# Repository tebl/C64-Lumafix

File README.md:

# C64 Lumafix

Based on Lumafix64 by e5frog over at the lemon64.com forums, this is a somewhat simplified version that should be easier to solder together for beginners with access to a reasonable set of soldering tools. Gone are the slightly confusing surface mount options that's mostly only suitable for those with more advanced skills or aim to have them premade with components from a fabrication company.

For those not familiar with the Lumafix board, this is a board that attempts to minimize the amount of vertical banding that to some extent occurrs on most Commodore 64 computers when connected to a modern TV (C64C and other short boards seem to be affected the most). It doesn't remove the problem completely since it doesn't solve the root cause of them, but it cancels out most of the effect - granting you the best visual clarity you can get from the original hardware! The board plugs in between the VIC-II chip and your Commodore 64 motherboard.

All of the components have, where applicable, been picked out so that it can be built as cheap as possible for people wanting to do this as a fun project in the home workshop (or kitchen table if that is what you have). For a complete list of components, see the BOM below. 

## Building the board
The recommended sequence of components to be soldered in place is as follows:

1. Check errata below for relevant changes
2. Read through the secion "Signal bypass" below if you have a revision B or later board, decide which functionality you want the board to have.
2. Solder in place the round pin headers into the position marked U2, the 40 pin strip should be cut in half so that you have two sections with 20 pins each. Take a look at the PCB, see two sections with 2x20 holes in them? These pins should be soldered on the top side of the PCB in the right set of 20 pin holes. The rest of the components from here on in are soldered on the backside as usual! You can use a spare 40 pin socket to ensure that the pins line up nicely before soldering them in place, if the board is going into a Commodore 64C you should shorten the pins with so that the board fits flush with the socket.
2. Solder in the three ceramic capacitors, note that C3 has a different value than the other two.
3. Solder in a 40 pin socket for U3, a 14 pin socket for U1. Note that sockets have an indent on one side indicating pin 1, this should be matched to a similar indent on the PCB silkscreen.
4. Solder the three potentiometers into place with the adjustment screw down towards the bottom. Temporarily hold them in place using tape to get the orientation just right if you like everything to be lined up perfectly, solder one pin in place and change orientation - heat up solder joint and reorient it until satisfied. Solder the rest of the pins now!

Inspect the board thoroughly until you are satisfied that none of the pins haven't been shorted together, to get a clean finish I recommend cleaning away any flux residue with some nail-polish remover without perfume (dilute it with a little IPA). Finally clean it again using IPA and some cotton buds. If you have access to the stuff, there are dedicated PCB-cleaning solutions that can be purchased though the first option can be easier to get depending on where you live.

### Signal bypass
When developing the [C64 Modulator Replacement](https://github.com/tebl/C64-Modulator-Replacement), there was an increase in the amount of visible jailbars on the screen (of the kind the Lumafix was made to smoothe over). This is due to crosstalk between video signals travelling across the motherboard in close proximity to other signals, the Lumafix attempts to remove these by adding the reverse of the same signals. I did however find that most of the issues disappear if the signals are run directly between the modulator board and the Lumafix with most of the circuitry no longer needed in this combination - video signals are wired directly to the modulator instad (bypassing the noise on the motherboard itself).

- If you want to build a standard revision B Lumafix board **without** replacing the modulator, then you should install two pieces of wire across the two jumpers marked CHR_SEP and LUM_SEP.
- If you want to build a standard revision B Lumafix board for use **with** the modulator replacement, install a piece of wire across pin 1-2 of the bottom potentiometer footprint. Run CHR/LUM wires from Lumafix board to the modulator replacement.

### Errata
- No issues noted so far, but thanks for checking!

## Installing the board
Did all the checking for shorts, board cleaning and ready to continue? If not, do so now (I'll wait)! Locate the VIC-II chip, it's a 40 pin IC like the board we just soldered together - mine was marked 8565 - to be sure you get the right one, check the [Wikipedia](https://en.wikipedia.org/wiki/MOS_Technology_VIC-II#List_of_VIC-II_versions) site for various IC version numbers to look for.

Now, this Commodore 64 you've opened up is probably over 30 years old so don't touch anything that you don't need to. When removing the IC it may appear stuck - don't yank on it, just carefully ease it out. If you don't have a dedicated IC-extractor, you _can_ use a flat screwdriver - just loosen it slightly from each side until it comes loose, take care not to scrape it against the motherboard under the socket! Insert the extracted IC into the board you just built, matching the indent to the socket while taking care that all pins goes into the socket and don't get stuck or bent underneath it. Insert the board into the now empty socket on the motherboard, taking care to match the orientation to the socket.

Turn all the potentiometers anti-clockwise all the way until you can hear you're at the beginning, with the Commodore 64 adjust the top one until you get the picture as good as it can get. The middle one will dial it in the rest of the way until you are completely satisfied with the startup screen on the Commodore 64. The bottom potentiometer adjusts phase-variance on the color signal, for this you may need to play around with it until you are satisfied with the results - mostly this will help alleviate slight ghosting effects on coloured objects on the screen, but for the most part just dial in the prettiest blue startup screen you can find and come back to it later if you find that you need to.

Note that the values dialed in will be very specific for the TV you'll be using, so test it out on the TV-setup you'll be using. Some TVs need more help than others, if you're lucky enough to still own a CRT you probably won't need this in the first place!

If you decided to build a revision B, or later version, of the Lumafix with signal bypass you need to run wires directly from the top of the board to the relevant points on the modulator replacement (these are labelled LUM and CHR on both boards, wire to the top pads on the modulator replacement board).

# Schematic
The supplied KiCad files should be sufficient as both a schematic and as a  starting point for ordering PCBs (basically you could just zip the contents of the export folder and upload that on a fabrication site), the schematic is also available in [PDF-format](https://github.com/tebl/C64-Lumafix/raw/master/export/Lumafix.pdf) and this is what you'll need to print and work your way through this things don't work as expected after assembly.

# BOM
Most parts should be easy to get a hold of from your favourite local electronic component shop, but given that I don't have access to such shops where I live so everything was based on whatever I could get cheapest from ebay/AliExpress (free shipping, plan on usually waiting 3-4 weeks though). You don't need the newest and fastest components, after all it's going into a 80s-era computer so don't go overboard unless you want to (you can replace 74LS ICs with 74HCT or 74ALS if you want something newer). Most components have been produced by various manufacturers, these mostly do the same thing without any relevant differences so just go for the cheapest.

Some vendors will have the same ICs in different form factors, the ones you want will often be specified as being in the form of a DIP/PDIP package. Usually you'll want sockets for each of the ICs as well, a bag of assorted sockets should be easily available without setting you back more than a couple bucks. With the sockets in place, you don't need to dread having to remove an IC later, this leads to easier fault finding and you can even "borrow" them for other projects later! For the pin headers, you should order the round pin ones since the standard ones will easily break the IC socket and you don't want to save pennies if it costs you a Commodore 64 mainboard!

| Reference    | Item                                  | Count |
| ------------ | ------------------------------------- | ----- |
| PCB          | Fabricate using Gerber files ([order](https://www.pcbway.com/project/shareproject/Commodore_64_Lumafix__revision_B_.html?inviteid=88707))  |     1 |
| C1-C2        | 47pf ceramic capacitor                |     2 |
| C3           | 100nF ceramic capacitor               |     1 |
| U1           | 74LS14 DIP-14                         |     1 |
| U2           | 40 pin round pin header (break in 2)  |     1 |
| U3           | DIP-40 IC Socket                      |     1 |
| RV1-RV3      | 3296W Potentiometer 2k Ohm            |     3 |

Please use the order link above when signing up to help me support this project, I'll get a small discount on future orders and hopefully that means I can afford to keep developing new and exciting modules in the future. By using the URL you won't have to deal with the rather daunting order forms for PCB fabrication, but if you want to go that route they'll probably want a zipped-up copy of the files in the export-directory!

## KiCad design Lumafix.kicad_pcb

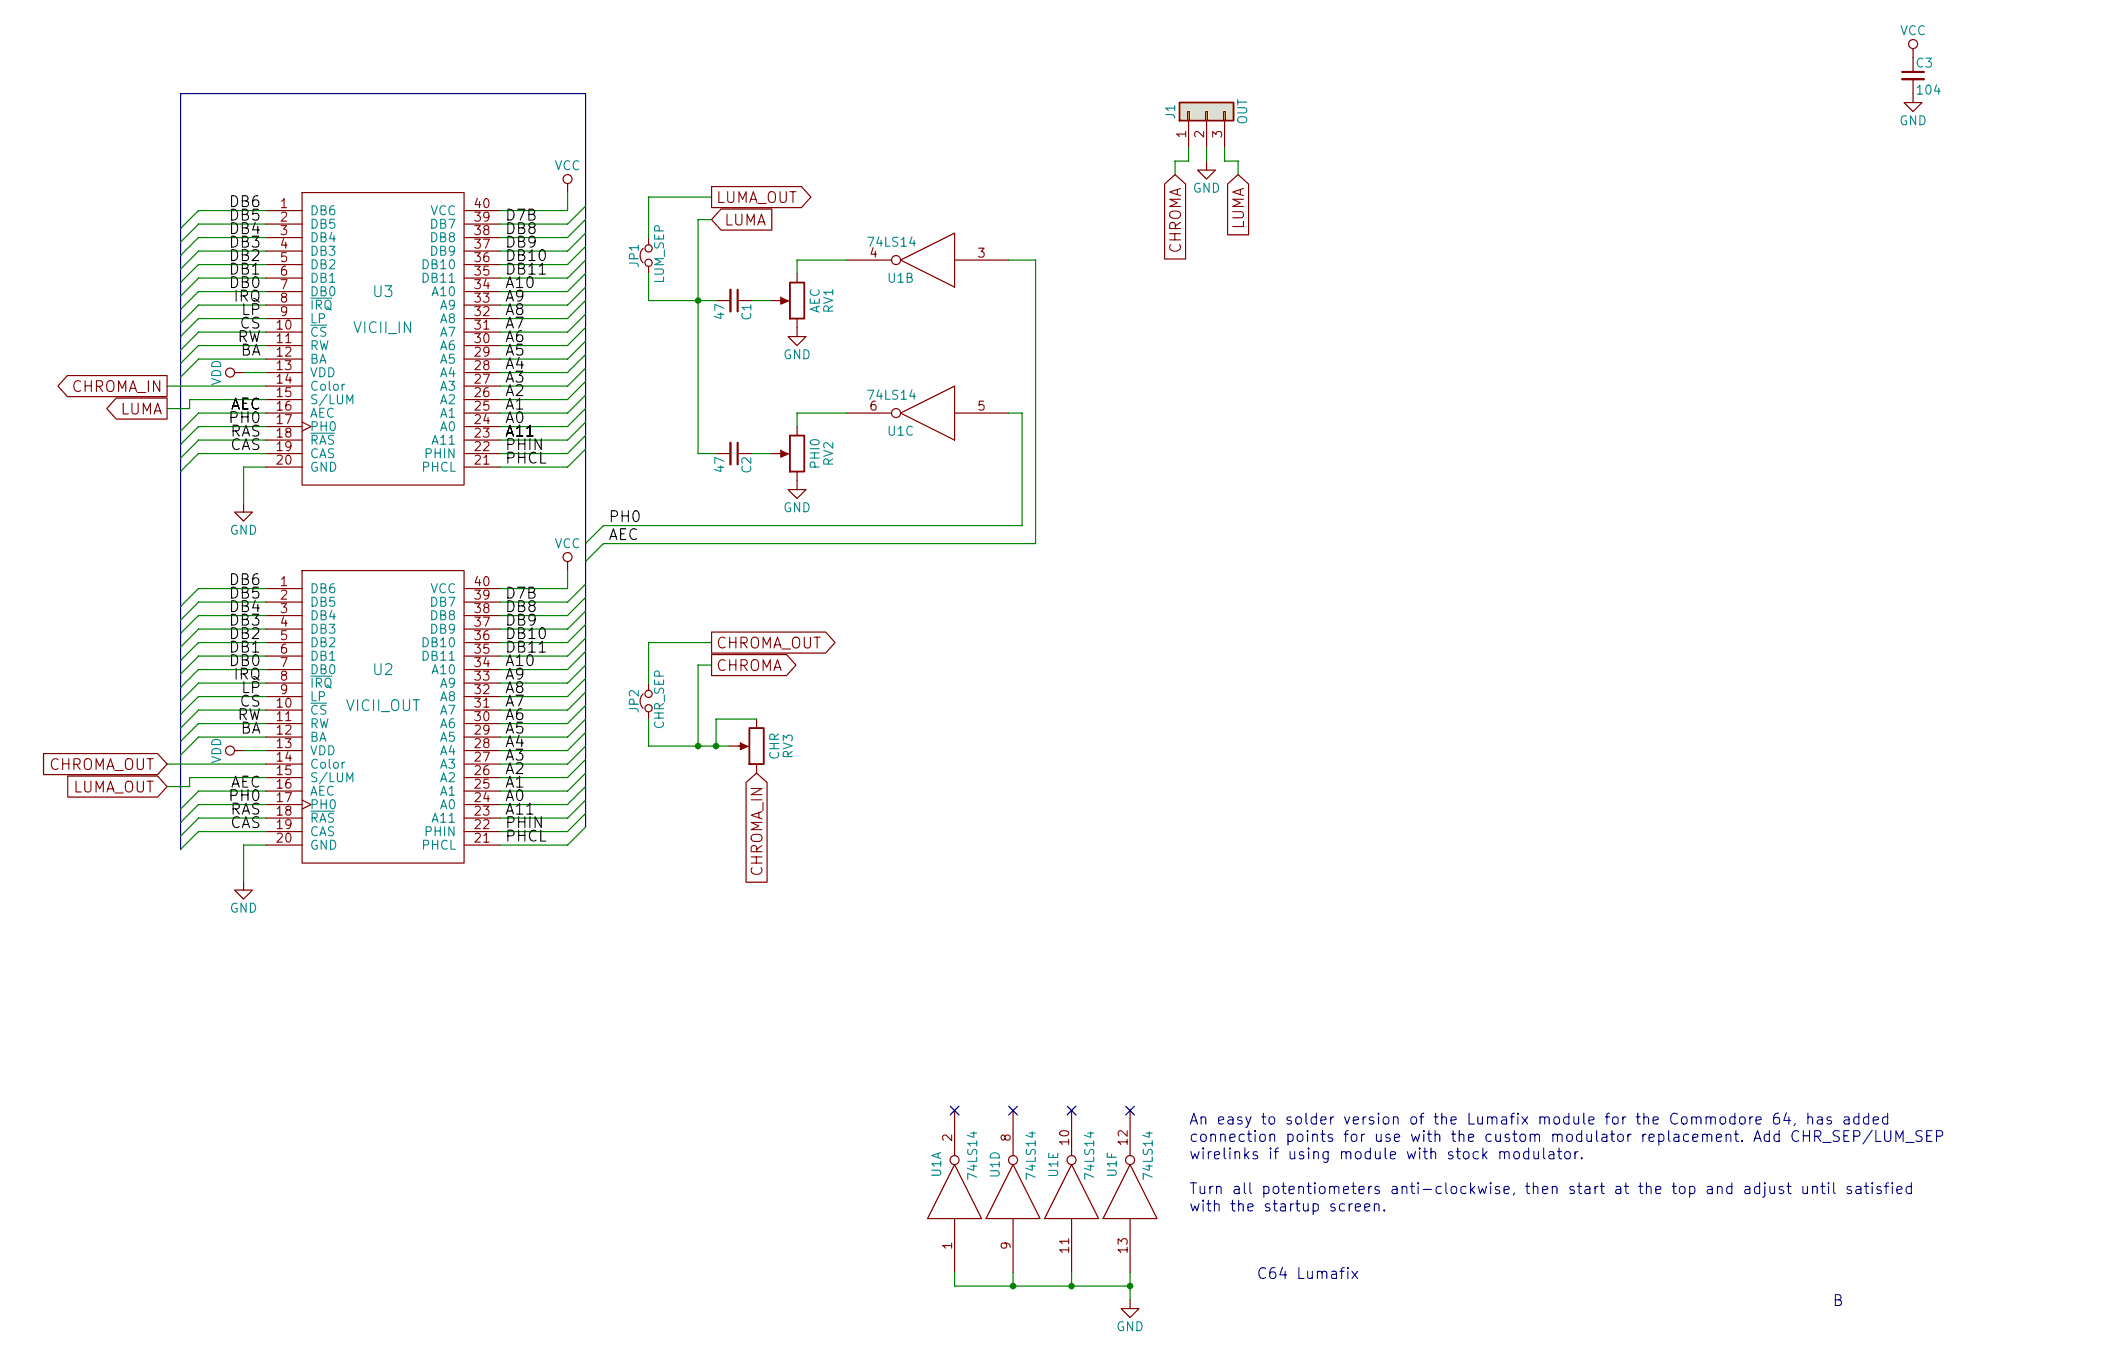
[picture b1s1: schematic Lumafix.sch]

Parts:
C1, C2: 47; C_Disc_D4.7mm_W2.5mm_P5.00mm
C3: 104; C_Disc_D4.7mm_W2.5mm_P5.00mm
J1: OUT; Pin_Header_Straight_1x03_Pitch2.54mm
JP1: LUM_SEP; Pin_Header_Straight_1x02_Pitch2.54mm
JP2: CHR_SEP; Pin_Header_Straight_1x02_Pitch2.54mm
RV1: AEC; Potentiometer_Trimmer_Bourns_3296W
RV2: PHI0; Potentiometer_Trimmer_Bourns_3296W
RV3: CHR; Potentiometer_Trimmer_Bourns_3296W
U1: 74LS14; DIP-14_W7.62mm_Socket
U2: VICII_OUT
U3: VICII_IN; DIP-40_W15.24mm_Socket

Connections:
/A0: U2.24 (A0), U3.24 (A0)
/A1: U2.25 (A1), U3.25 (A1)
/A2: U2.26 (A2), U3.26 (A2)
/A3: U2.27 (A3), U3.27 (A3)
/A4: U2.28 (A4), U3.28 (A4)
/A5: U2.29 (A5), U3.29 (A5)
/A6: U2.30 (A6), U3.30 (A6)
/A7: U2.31 (A7), U3.31 (A7)
/A8: U2.32 (A8), U3.32 (A8)
/A9: U2.33 (A9), U3.33 (A9)
/A10: U2.34 (A10), U3.34 (A10)
/A11: U2.23 (A11), U3.23 (A11)
/AEC: U1.3, U2.16 (AEC), U3.16 (AEC)
/BA: U2.12 (BA), U3.12 (BA)
/CAS: U2.19 (CAS), U3.19 (CAS)
/CS: U2.10 (~CS), U3.10 (~CS)
/D7B: U2.39 (DB7), U3.39 (DB7)
/DB0: U2.7 (DB0), U3.7 (DB0)
/DB1: U2.6 (DB1), U3.6 (DB1)
/DB2: U2.5 (DB2), U3.5 (DB2)
/DB3: U2.4 (DB3), U3.4 (DB3)
/DB4: U2.3 (DB4), U3.3 (DB4)
/DB5: U2.2 (DB5), U3.2 (DB5)
/DB6: U2.1 (DB6), U3.1 (DB6)
/DB8: U2.38 (DB8), U3.38 (DB8)
/DB9: U2.37 (DB9), U3.37 (DB9)
/DB10: U2.36 (DB10), U3.36 (DB10)
/DB11: U2.35 (DB11), U3.35 (DB11)
/IRQ: U2.8 (~IRQ), U3.8 (~IRQ)
/LP: U2.9 (LP), U3.9 (LP)
/PH0: U1.5, U2.17 (PH0), U3.17 (PH0)
/PHCL: U2.21 (PHCL), U3.21 (PHCL)
/PHIN: U2.22 (PHIN), U3.22 (PHIN)
/RAS: U2.18 (~RAS), U3.18 (~RAS)
/RW: U2.11 (RW), U3.11 (RW)
CHROMA: J1.1, JP2.1, RV3.2, RV3.3
CHROMA_IN: RV3.1, U3.14 (Color)
CHROMA_OUT: JP2.2, U2.14 (Color)
GND: C3.2, J1.2, RV1.1, RV2.1, U1.1, U1.7 (GND), U1.9, U1.11, U1.13, U2.20 (GND), U3.20 (GND)
LUMA: C1.2, C2.2, J1.3, JP1.1, U3.15 (S/LUM)
LUMA_OUT: JP1.2, U2.15 (S/LUM)
unnamed: C1.1, RV1.2
unnamed: C2.1, RV2.2
unnamed: RV1.3, U1.4
unnamed: RV2.3, U1.6
VCC: C3.1, U1.14 (VCC), U2.40 (VCC), U3.40 (VCC)
VDD: U2.13 (VDD), U3.13 (VDD)

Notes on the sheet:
C64 Lumafix
An easy to solder version of the Lumafix module for the Commodore 64, has added connection points for use with the custom modulator replacement. Add CHR_SEP/LUM_SEP wirelinks if using module with stock modulator. Turn all potentiometers anti-clockwise, then start at the top and adjust until satisfi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

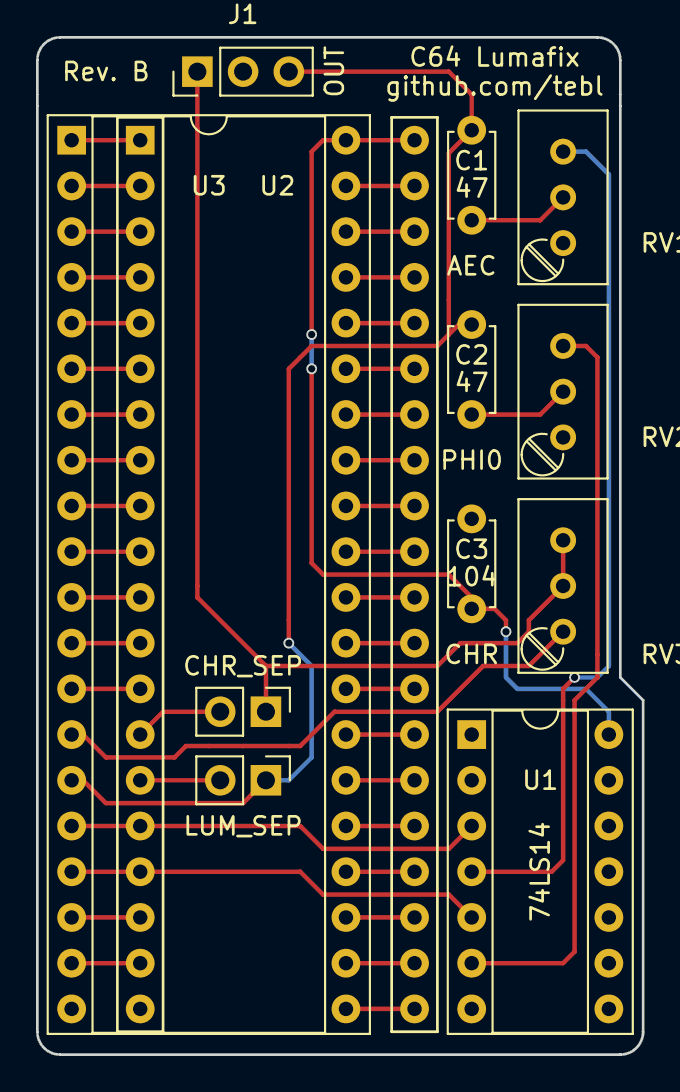
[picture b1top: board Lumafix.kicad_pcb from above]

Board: 2 copper layers, 33.7 x 56.5 mm, 12 parts (0 on the bottom side), 47 nets.

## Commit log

2018-09-03 Basic schematic (passthrough only)
2018-09-11 Schematic completed
2018-09-11 PCB layout and gerber export
2018-09-11 Added readme
2018-10-05 Exported schematic
2018-10-05 Added proper readme with build details and BOM.
2018-10-05 Misspelled CLR on PCB, oops!
2018-10-09 Added shared project link to pcbway
2018-10-09 Added gallery images
2018-10-09 Fixed README, added images...
2019-08-17 Added signal bypass to module as rev. B
2019-08-20 Gerber export
2019-10-18 Added notes to silkscreen
2019-10-18 Rev B passthrough illustration
2019-10-18 Descriptions added for revision B
2019-12-25 Update PCBway project URL
